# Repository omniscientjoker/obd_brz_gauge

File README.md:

# OBD BRZ Gauge

A round ESP-IDF car gauge for the Waveshare ESP32-S3-Touch-LCD-1.85. It connects
to an ELM327-compatible BLE OBD adapter, reads vehicle data, and renders a
touch UI with LVGL.

基于 ESP-IDF 的圆形车载仪表，硬件为微雪 Waveshare ESP32-S3-Touch-LCD-1.85。
通过 BLE 连接兼容 ELM327 的 OBD 适配器读取车辆数据，用 LVGL 渲染触控界面。

**[效果演示 / Demo video](https://www.douyin.com/video/7614174567678984187)**

> Based on [zhaizhaitao/open_obd_dsp](https://github.com/zhaizhaitao/open_obd_dsp)
> by zhaizhaitao ([Bilibili demo](https://www.bilibili.com/video/BV18oHXz6EiQ/)).
> This is a derivative with additional vehicle profiles, multi-gauge support and
> a theming system.
>
> 本项目基于 [zhaizhaitao/open_obd_dsp](https://github.com/zhaizhaitao/open_obd_dsp)
> 二次开发，原作者 zhaizhaitao（[B 站演示](https://www.bilibili.com/video/BV18oHXz6EiQ/)）。
> 本仓库新增了多车型适配、三连表联动和主题系统。

---

## ⚠️ Branch Notice / 分支说明

This repository has two main branches with **incompatible partition layouts**:

- **`main`** — Stable branch, themes compiled into firmware
- **`theme-upgrade`** — Experimental branch with runtime-loadable themes (4MB theme partition)

⚠️ You **cannot** OTA upgrade between branches. See [docs/BRANCH_COMPARISON.md](docs/BRANCH_COMPARISON.md) for details.

本仓库有两个主要分支，**分区布局不兼容**：

- **`main`** — 稳定分支，主题编译进固件
- **`theme-upgrade`** — 实验分支，支持运行时加载主题（4MB 主题分区）

⚠️ 两个分支之间**无法通过 OTA 互相升级**。详见 [docs/BRANCH_COMPARISON.md](docs/BRANCH_COMPARISON.md)。

---

## 📖 Documentation / 文档索引

**Start here / 从这里开始**

| Document | What it covers / 内容 |
|----------|----------------------|
| [docs/README.zh-CN.md](docs/README.zh-CN.md) | **完整中文说明** — 功能、依赖、编译烧录、适配要点 |
| [docs/README.en.md](docs/README.en.md) | **Full English guide** — features, requirements, build and flash |
| [docs/BRANCH_COMPARISON.md](docs/BRANCH_COMPARISON.md) | **Branch differences** — main vs theme-upgrade partition layouts / 分支差异对比 |
| [docs/APP_INTEGRATION.md](docs/APP_INTEGRATION.md) | App/device manifest, firmware validation, single-slot boot animation / App 对接、硬件校验、单槽开机动画 |
| [firmware/README.md](firmware/README.md) | Pre-built binaries and flash addresses / 预编译固件与烧录地址 |
| [CHANGELOG.md](CHANGELOG.md) | Changelog / 更新日志（中英双语） |

**Vehicles & OBD / 车辆适配与 OBD**

| Document | What it covers / 内容 |
|----------|----------------------|
| [docs/VEHICLE_CONFIG.md](docs/VEHICLE_CONFIG.md) | **Adding a vehicle profile** / 新增车型看这篇（中英对照） |
| [docs/OBD_TROUBLESHOOTING.md](docs/OBD_TROUBLESHOOTING.md) | No data / won't connect — diagnosis / 连不上或没数据时的排查 |
| [docs/AUTO_PROTOCOL_DETECTION.md](docs/AUTO_PROTOCOL_DETECTION.md) | Protocol auto-detection: usage, FAQ, debugging / 自动协议检测：用法、常见问题、调试 |
| [docs/BRZ_ZD8_PROTOCOL_GUIDE.md](docs/BRZ_ZD8_PROTOCOL_GUIDE.md) | BRZ ZD8 (Gen2) protocol diagnosis / ZD8 协议诊断 |
| [docs/OBD_PROTOCOL_COMPOSITION_DESIGN.zh-CN.md](docs/OBD_PROTOCOL_COMPOSITION_DESIGN.zh-CN.md) | **Multi-protocol composition architecture** / 多协议组合、覆盖和迁移架构 |
| [docs/FORD_TPMS_CAPTURE.md](docs/FORD_TPMS_CAPTURE.md) | Ford TPMS UDS/CAN validation procedure / 福特胎压 UDS/CAN 验证流程 |

**UI themes / 界面主题**

| Document | What it covers / 内容 |
|----------|----------------------|
| [themes/README.md](themes/README.md) | **Build a theme** — no C code needed / 做一套主题（中英双语） |
| [docs/THEMING.md](docs/THEMING.md) | Theme framework internals / 主题框架内部实现 |

Repository layout is in [this README](#repository-layout--目录结构) below.
目录结构见本文下方的[目录结构](#repository-layout--目录结构)一节。

---

## Status / 当前状态

| | |
|---|---|
| Hardware / 硬件 | Waveshare ESP32-S3-Touch-LCD-1.85 (360×360 round, 16 MB flash, 8 MB PSRAM) |
| Stack / 软件栈 | ESP-IDF 5.5.3, LVGL 8 |
| Link / 通信链路 | BLE + ELM327 — standard OBD PID; only ZN/C6 CAN keeps ATMA monitoring |
| Multi-gauge / 三连表 | One master + multiple slaves over ESP-NOW / 一主多从，ESP-NOW 联动 |
| OBD architecture / 架构 | Composed common rules + vehicle packs + special handlers, with legacy fallback / 通用规则、车型包、特殊处理器组合，保留兼容回退 |
| Verified on / 已验证 | Subaru BRZ ZN/C6 (fully); Ford Mondeo 2014 2.0T BCMii TPMS / BRZ ZN/C6 已完整验证；蒙迪欧 2014 2.0T BCMii 胎压已验证 |

**Vehicle profiles / 内置车型** (18) — full list in
[vehicle_profiles.c](main/app_obd_dsp/vehicle_profiles.c), selectable in Settings:

`OBD2 Generic` · `ZN/C6 CAN` · `ZN/C6 PID` · `ZD8 OBD` · `ZD8` · `MX-5 ND` ·
`BMW F/G` · `Supra A90` · `BMW G OBD` · `BMW E` · `JCW F56` · `MINI R55` ·
`POS 997.2` · `POS 997.1` · `GIULIA 2.0T` · `jeep` · `Honda Integra` ·
`Ford Mondeo 2014` (BCMii TPMS, validated)

## Highlights / 主要特性

- **CAN broadcast monitoring** — only `ZN/C6 CAN` bypasses PID polling for
  high-rate channels; the rest stay on OBD-only polling. / **CAN 广播帧监听** —— 仅 `ZN/C6 CAN` 使用高速监听，其余车型保持 OBD 轮询。
- **Single-thread ELM327 loop** — no mixed OBD/CAN parallel path; only `ZN/C6 CAN`
  uses ATMA, so the adapter does not get contended by dual polling. /
  **ELM327 单线程轮询** —— 不再混跑 OBD/CAN；只有 `ZN/C6 CAN` 走 ATMA，避免适配器抢占和数据延迟。
- **Brake-temp / oil-pressure alarm throttle** — these two alarms are rate-limited
  to once every 30 seconds. / **刹车温度 / 油压报警节流** —— 两项报警限制为 30 秒一次，减少刷屏。
- **Multi-gauge over ESP-NOW** — one board reads OBD and broadcasts; the others
  display with zero extra OBD load, paired over real BLE. /
  **三连表** —— 主表读 OBD 广播，从表零额外负载显示，走真蓝牙配对。
- **Data-driven themes** — a theme is a folder with a manifest plus optional
  artwork; no C code. / **配置驱动主题** —— 一个文件夹 + 一份清单，不用写 C。
- **BLE device manifest** — a read-only GATT service exposes hardware/build info so the App can reject mismatched firmware before flashing. / **BLE 设备清单** —— 只读 GATT 服务暴露硬件/构建信息，App 刷写前先做硬件匹配校验。
- **RPM warning, incl. linked mode** — three gauges light up in sequence as revs
  climb. / **转速报警（含联动模式）** —— 三块表随转速依次亮起。
- Manufacturer oil-temp paths beyond PID 01 5C (Mode 21/22, Mazda, MINI/BMW),
  per-vehicle protocol lock, gear from CAN when available.
- **Composable OBD rules** — common SAE PID rules, vehicle-specific UDS/CAN packs,
  stable-ID overrides, special-handler capabilities, and fail-closed plan validation.
- Self-healing BLE: re-initializes on reconnect and recovers when data stalls —
  no manual reconnect after ignition. / 数据中断自愈，上车通电无需手动重连。

Full feature lists: [中文](docs/README.zh-CN.md#功能概览) ·
[English](docs/README.en.md#features)

## Quick Start / 快速开始

### Build from source / 从源码编译

```bash
git clone https://github.com/steveEcode/obd_brz_gauge.git
cd obd_brz_gauge
./tools/build_gauge_firmware.sh master
./tools/build_gauge_firmware.sh slave
python3 tools/gen_release.py
```

### Flash pre-built firmware / 烧录预编译固件

Activate ESP-IDF v5.5.3 before building. Master and slave use separate build
directories and configurations. See [firmware/README.md](firmware/README.md).

激活 ESP-IDF v5.5.3 后编译。主表和从表分别构建；`tools/release.sh` 可一次构建并打包两套固件。

Flash the master package / 烧录主表包：

```bash
cd firmware/release/master
python -m esptool --chip esp32s3 -p PORT -b 460800 \
  --before default_reset --after hard_reset write_flash @flash_args
```

For a slave, run the same command inside `firmware/release/slave`.
从表在 `firmware/release/slave` 目录中执行同样命令。两块从表刷入同一份固件。

**Notes / 说明:**
- Replace `PORT` with your serial port (e.g., `COM3` on Windows, `/dev/ttyUSB0` on Linux, `/dev/cu.usbserial-*` on macOS)
- Requires [esptool.py](https://github.com/espressif/esptool) installed: `pip install esptool`
- Writes the specified partitions; preserves NVS and theme data
- For subsequent OTA updates, use the companion mobile app

- 将 `PORT` 替换为你的串口（Windows: `COM3`，Linux: `/dev/ttyUSB0`，macOS: `/dev/cu.usbserial-*`）
- 需要安装 [esptool.py](https://github.com/espressif/esptool)：`pip install esptool`
- 烧录指定分区，保留 NVS 设置和主题数据
- 后续升级请使用配套手机 App 进行 OTA 更新

## Repository Layout / 目录结构

| Path | Contents |
|------|----------|
| [main/app_main.c](main/app_main.c) | Entry point: hardware, LVGL, BLE and task startup |
| [main/app_obd_dsp](main/app_obd_dsp) | OBD data cache, vehicle profiles, CAN decoders, boot media |
| [main/bsp_obd_dsp](main/bsp_obd_dsp) | Board support: BLE, NVS, LCD, touch, I2C, IO expander, ESP-NOW |
| [main/export_path](main/export_path) | LVGL UI (SquareLine export) + theme framework |
| [themes](themes) | Theme manifests and artwork / 主题清单与素材 |
| [bootmedia](bootmedia) | Boot animation blocks (SPIFFS partition source) |
| [tools](tools) | Helper scripts: theme codegen, image conversion, boot blocks |
| [firmware/release](firmware/release) | Pre-compiled binaries |
| [model](model) | 3D printable housings, gauge pods and brackets |
| [docs](docs) | Documentation (see index above) |

## 3D Models / 开源模型

| File | Description |
|------|-------------|
| `model/esp32_1.85_weixue/housing.stl` | Board housing / 开发板外壳 |
| `model/Subaru/brz_zc_n6/triple_gauge_pod.stp` | BRZ ZN/C6 triple gauge pod / 三连表底座 |
| `model/Subaru/brz_zc_n6/passenger_dashboard_scan.stl` | BRZ ZN/C6 passenger dash scan (fitting reference) / 副驾仪表台扫描件 |
| `model/mazda/mx5_nd/air_vent_bracket.stl` | MX-5 ND air vent bracket / 出风口支架 |

## Porting Notes / 适配提醒

This repository contains board-specific adaptation and UI resources. Porting to
another ESP32-S3 board means revisiting pin mapping and display settings
([main/bsp_obd_dsp](main/bsp_obd_dsp)); porting to another car means
re-verifying BLE services, PIDs and response parsing
([docs/VEHICLE_CONFIG.md](docs/VEHICLE_CONFIG.md)).

仓库内是针对当前开发板的适配代码和 UI 资源。换开发板需要重新检查引脚定义和屏幕参数；
换车型或适配器需要重新验证 BLE 服务、PID 和返回数据解析。

## Acknowledgments / 致谢

- [Hokori23](https://github.com/Hokori23) — performance optimization suggestions
  and contributions (NVS flush lock hold-time, page-aware refresh cadence, OBD
  polling throughput). / 性能优化建议与贡献。
- [timurrrr/ft86](https://github.com/timurrrr/ft86) — comprehensive FT86 CAN bus
  documentation (Gen1/Gen2 CAN ID mappings and byte-level decoding formulas),
  which made the CAN broadcast monitoring possible. /
  提供了完整的 FT86 CAN 总线文档，使 CAN 广播帧监听得以实现。

## License / 开源协议

This project is licensed under the **GNU General Public License v3.0 (GPLv3)**.

本项目采用 **GNU 通用公共许可证 v3.0 (GPLv3)** 开源协议。

- You are free to use, modify, and distribute this software.
- If you distribute modified versions, you must also release the source code under GPLv3.
- See [LICENSE](LICENSE) for the full license text.

**简单来说**：
- ✅ 可以自由使用、修改和分发本软件
- ⚠️ 如果分发修改版本，必须同样以GPLv3协议开源代码
- 🔒 增强了防专利条款和Tivoization保护
- 📄 完整协议文本见 [LICENSE](LICENSE) 文件

```
Copyright (C) 2024-2026  steveEcode and contributors

This program is free software: you can redistribute it and/or modify
it under the terms of the GNU General Public License as published by
the Free Software Foundation, either version 3 of the License, or
(at your option) any later version.

This program is distributed in the hope that it will be useful,
but WITHOUT ANY WARRANTY; without even the implied warranty of
MERCHANTABILITY or FITNESS FOR A PARTICULAR PURPOSE.  See the
GNU General Public License for more details.
```

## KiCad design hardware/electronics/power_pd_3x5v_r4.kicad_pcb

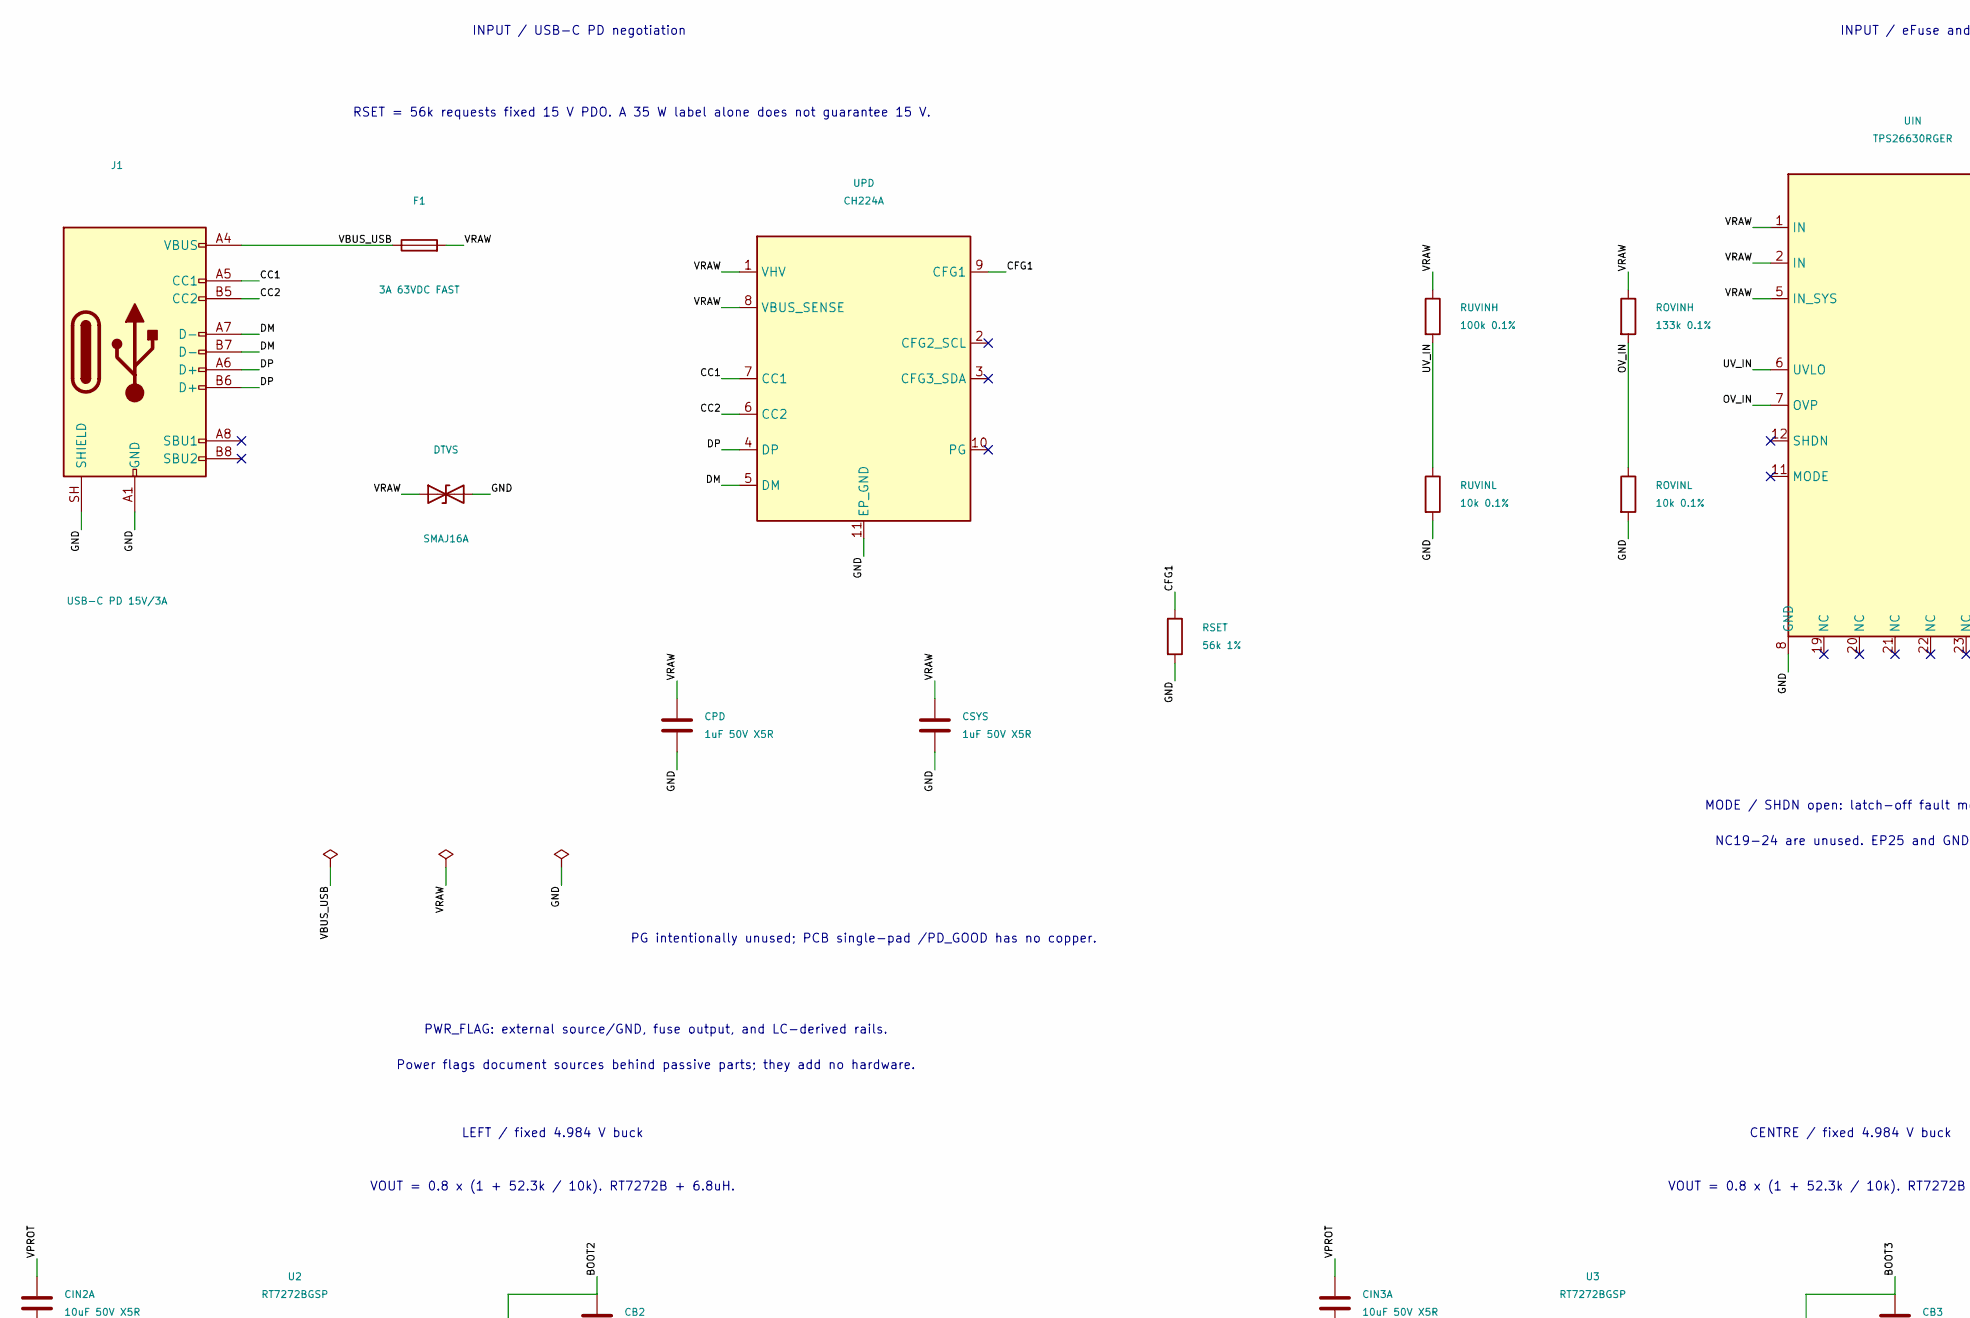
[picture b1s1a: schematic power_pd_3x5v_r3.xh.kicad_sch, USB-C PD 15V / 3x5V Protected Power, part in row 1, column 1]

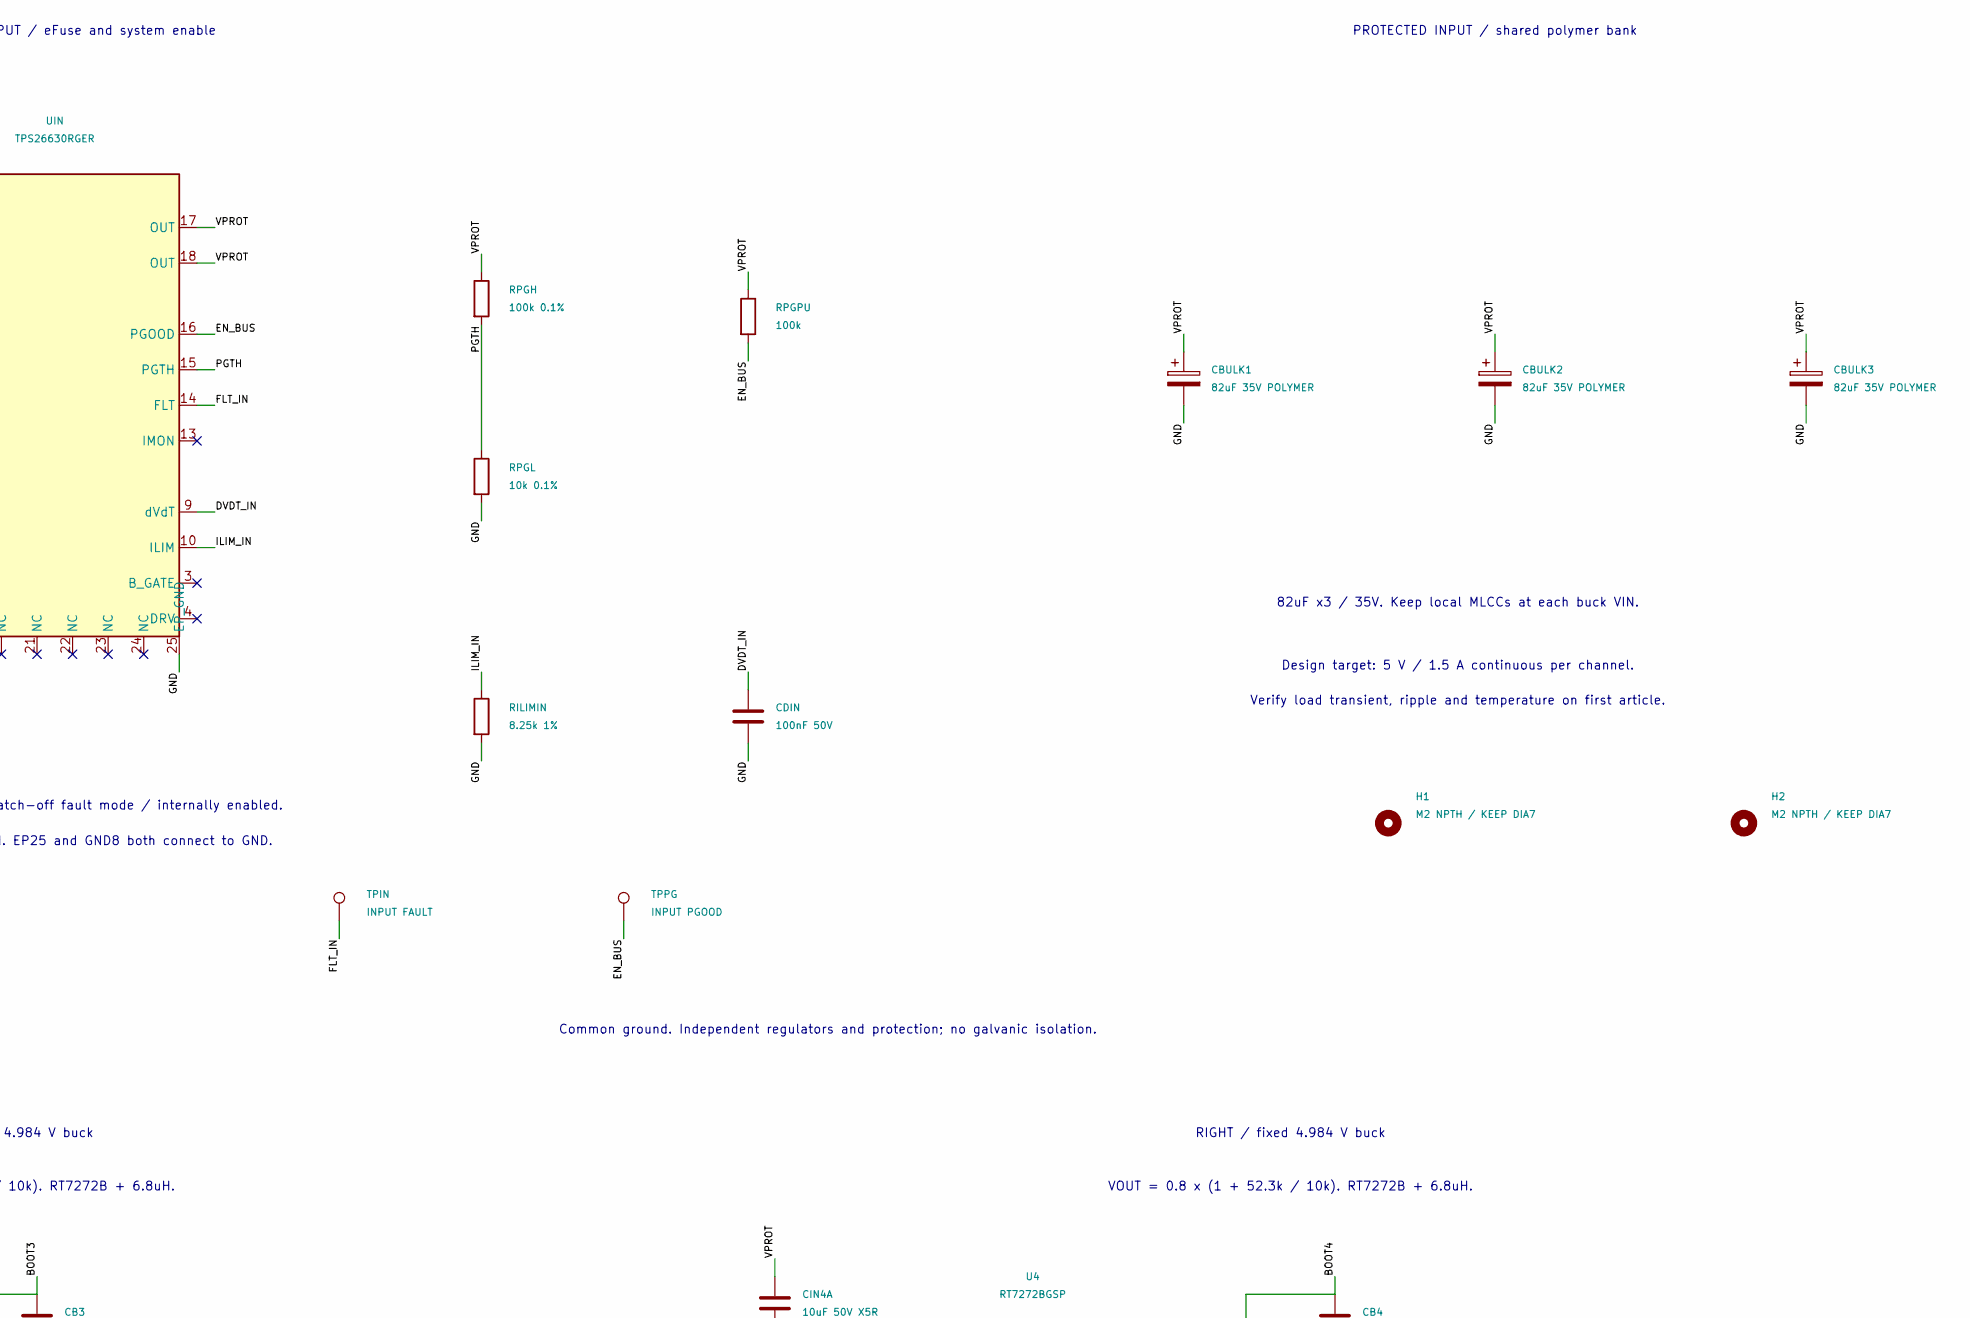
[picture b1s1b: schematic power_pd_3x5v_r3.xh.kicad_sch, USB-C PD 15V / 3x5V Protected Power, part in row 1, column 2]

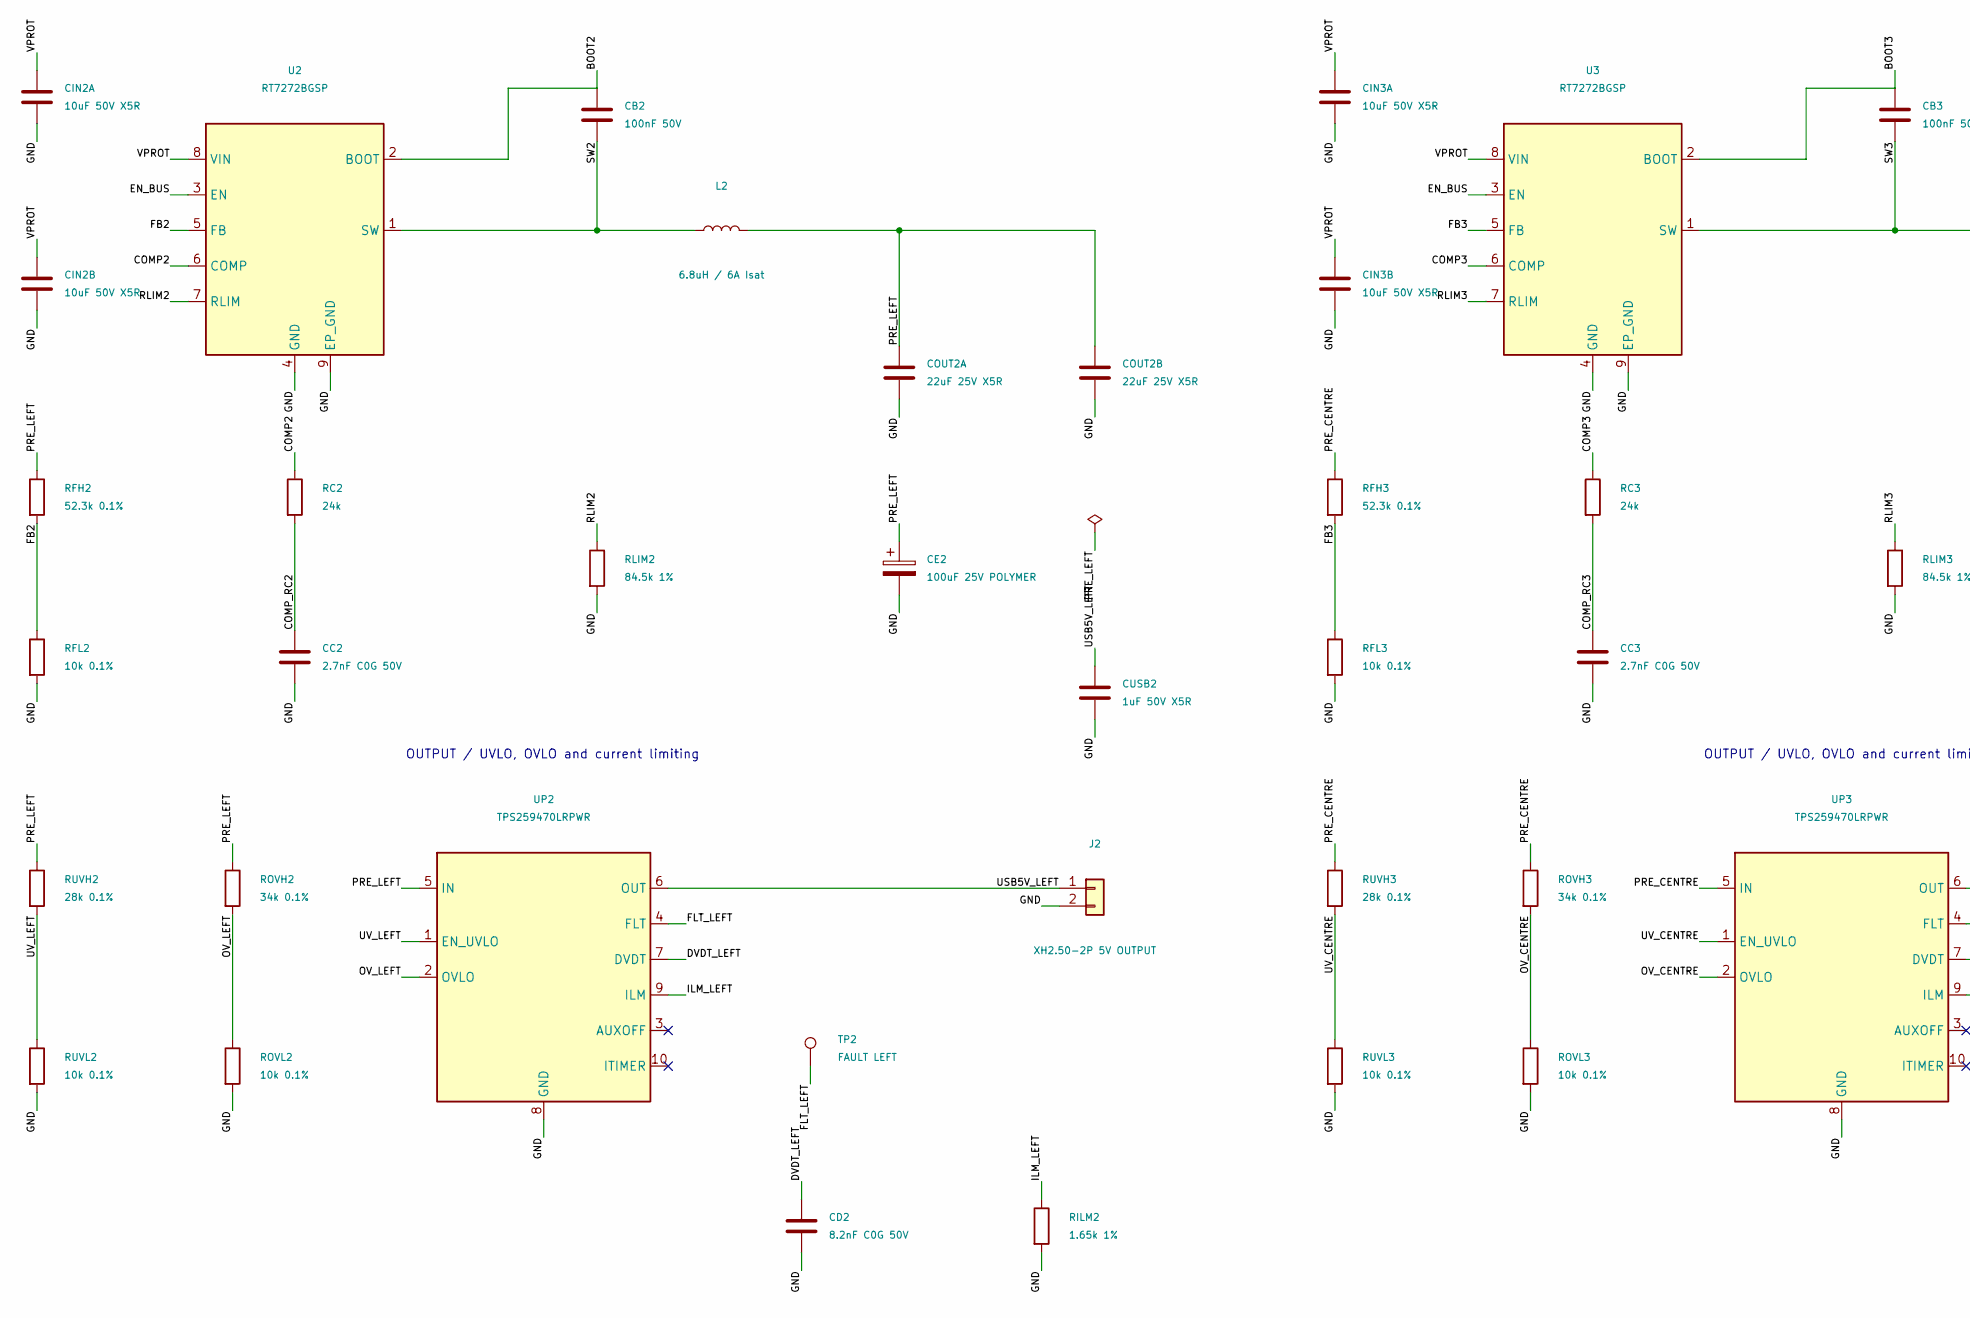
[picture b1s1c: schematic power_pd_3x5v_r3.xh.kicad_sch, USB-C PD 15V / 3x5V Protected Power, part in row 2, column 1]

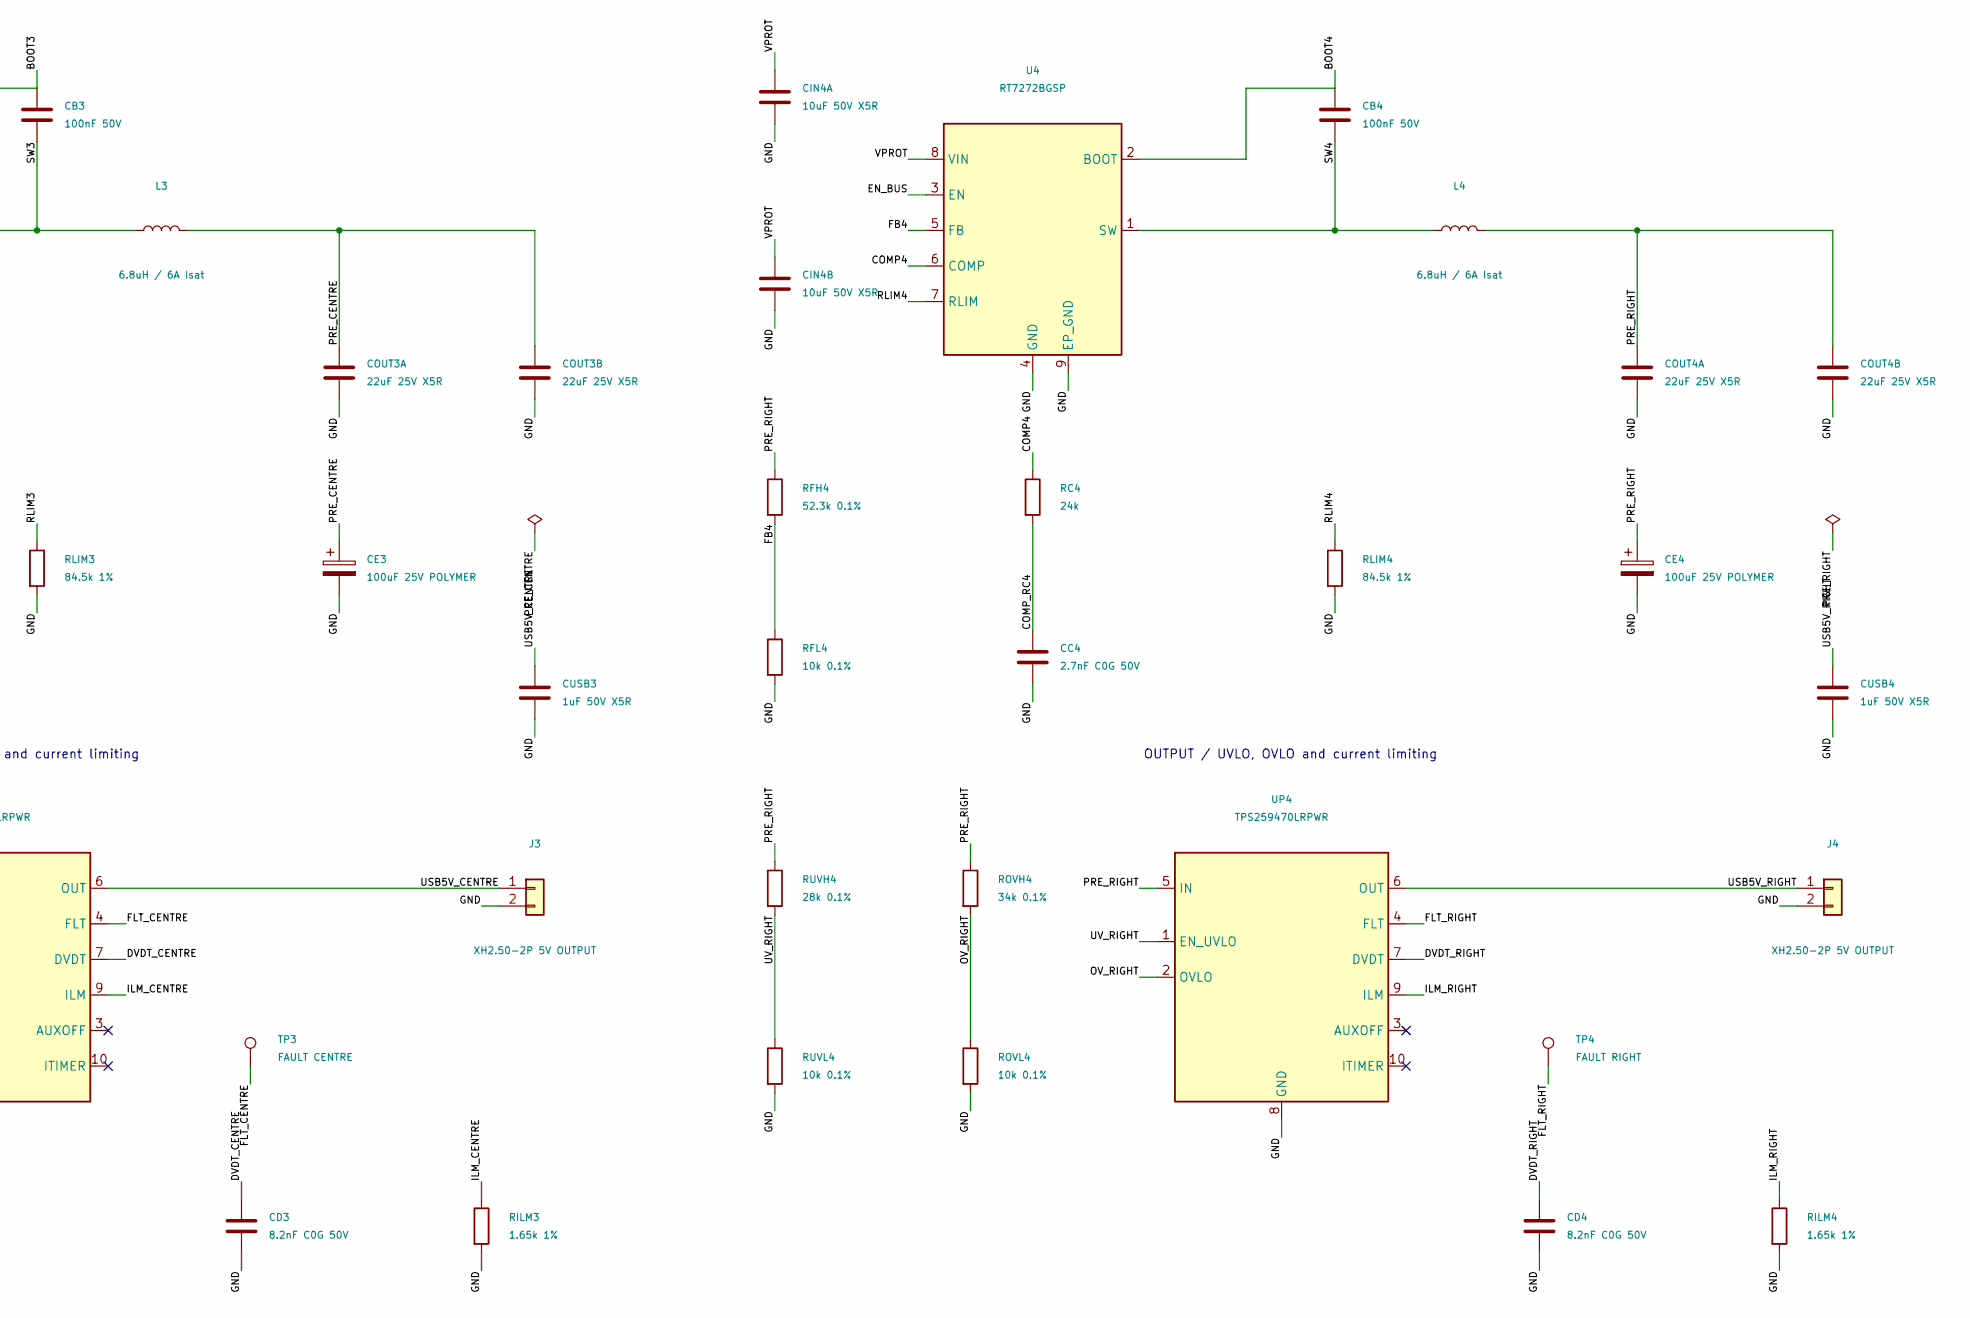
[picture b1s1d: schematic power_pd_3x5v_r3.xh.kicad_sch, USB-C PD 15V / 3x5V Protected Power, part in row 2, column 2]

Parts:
CB2, CB3, CB4: 100nF 50V; C_0603_1608Metric; MPN GRM188R71H104KA93D
CBULK1, CBULK2, CBULK3: 82uF 35V POLYMER; CP_Elec_8x6.9; MPN 35SVPK82M
CC2, CC3, CC4: 2.7nF C0G 50V; C_0603_1608Metric; MPN GRM1885C1H272JA01D
CD2, CD3, CD4: 8.2nF C0G 50V; C_0603_1608Metric; MPN GRM1885C1H822JA01D
CDIN: 100nF 50V; C_0603_1608Metric; MPN GRM188R71H104KA93D
CE2, CE3, CE4: 100uF 25V POLYMER; CP_Elec_8x6.9; MPN 25SVPF100M
CIN2A, CIN2B, CIN3A, CIN3B, CIN4A, CIN4B: 10uF 50V X5R; C_1206_3216Metric; MPN GRM31CR61H106KA12L
COUT2A, COUT2B, COUT3A, COUT3B, COUT4A, COUT4B: 22uF 25V X5R; C_1206_3216Metric; MPN GRM31CR61E226KE15L
CPD: 1uF 50V X5R; C_0603_1608Metric; MPN GRM188R61H105KAALD
CSYS: 1uF 50V X5R; C_0603_1608Metric; MPN GRM188R61H105KAALD
CUSB2, CUSB3, CUSB4: 1uF 50V X5R; C_0603_1608Metric; MPN GRM188R61H105KAALD
DTVS: SMAJ16A; D_SMA; MPN SMAJ16A-E3/61
F1: 3A 63VDC FAST; SF_1206F_Recommended; MPN SF-1206F300-2
H1, H2: M2 NPTH / KEEP DIA7; M2_NPTH_2.4mm
J1: USB-C PD 15V/3A; USB_C_Receptacle_GCT_USB4085; MPN USB4085-GF-A
J2, J3, J4: XH2.50-2P 5V OUTPUT; JST_XH_S2B-XH-A_1x02_P2.50mm_Horizontal_Assembly; MPN S2B-XH-A(LF)(SN)
L2, L3, L4: 6.8uH / 6A Isat; L_Coilcraft_XAL5050-XXX; MPN XAL5050-682MEC
RC2, RC3, RC4: 24k; R_0603_1608Metric; MPN TNPW060324K0FEEA
RFH2, RFH3, RFH4: 52.3k 0.1%; R_0603_1608Metric; MPN TNPW060352K3BEEA
RFL2, RFL3, RFL4: 10k 0.1%; R_0603_1608Metric; MPN TNPW060310K0BEEA
RILIMIN: 8.25k 1%; R_0603_1608Metric; MPN TNPW06038K25FEEA
RILM2, RILM3, RILM4: 1.65k 1%; R_0603_1608Metric; MPN TNPW06031K65FEEA
RLIM2, RLIM3, RLIM4: 84.5k 1%; R_0603_1608Metric; MPN TNPW060384K5FEEA
ROVH2, ROVH3, ROVH4: 34k 0.1%; R_0603_1608Metric; MPN TNPW060334K0BEEA
ROVINH: 133k 0.1%; R_0402_1005Metric; MPN CRT0402-BY-1333GLF
ROVINL: 10k 0.1%; R_0402_1005Metric; MPN TNPW040210K0BEED
ROVL2, ROVL3, ROVL4: 10k 0.1%; R_0603_1608Metric; MPN TNPW060310K0BEEA
RPGH: 100k 0.1%; R_0603_1608Metric; MPN TNPW0603100KBEEA
RPGL: 10k 0.1%; R_0603_1608Metric; MPN TNPW060310K0BEEA
RPGPU: 100k; R_0603_1608Metric; MPN TNPW0603100KFEEA
RSET: 56k 1%; R_0603_1608Metric; MPN TNPW060356K0FEEA
RUVH2, RUVH3, RUVH4: 28k 0.1%; R_0603_1608Metric; MPN TNPW060328K0BEEA
RUVINH: 100k 0.1%; R_0402_1005Metric; MPN TNPW0402100KBEED
RUVINL: 10k 0.1%; R_0402_1005Metric; MPN TNPW040210K0BEED
RUVL2, RUVL3, RUVL4: 10k 0.1%; R_0603_1608Metric; MPN TNPW060310K0BEEA
TP2: FAULT LEFT; TestPoint_Pad_D1.0mm
TP3: FAULT CENTRE; TestPoint_Pad_D1.0mm
TP4: FAULT RIGHT; TestPoint_Pad_D1.0mm
TPIN: INPUT FAULT; TestPoint_Pad_D1.0mm
TPPG: INPUT PGOOD; TestPoint_Pad_D1.0mm
U2, U3, U4: RT7272BGSP; RT7272BGSP_PSOP8_Option2; MPN RT7272BGSP
UIN: TPS26630RGER; Texas_RGE0024H_VQFN-24-1EP_4x4mm_P0.5mm_EP2.7x2.7mm_Assembly; MPN TPS26630RGER
UP2, UP3, UP4: TPS259470LRPWR; TI_RPW0010A; MPN TPS259470LRPWR
UPD: CH224A; SSOP-10-1EP_3.9x4.9mm_P1mm_EP2.1x3.3mm; MPN CH224A

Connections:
/BOOT2: CB2.1, U2.2 (BOOT)
/BOOT3: CB3.1, U3.2 (BOOT)
/BOOT4: CB4.1, U4.2 (BOOT)
/CC1: J1.A5 (CC1), UPD.7 (CC1)
/CC2: J1.B5 (CC2), UPD.6 (CC2)
/CFG1: RSET.1, UPD.9 (CFG1)
/COMP2: RC2.1, U2.6 (COMP)
/COMP3: RC3.1, U3.6 (COMP)
/COMP4: RC4.1, U4.6 (COMP)
/COMP_RC2: CC2.1, RC2.2
/COMP_RC3: CC3.1, RC3.2
/COMP_RC4: CC4.1, RC4.2
/DM: J1.A7 (D-), J1.B7 (D-), UPD.5 (DM)
/DP: J1.A6 (D+), J1.B6 (D+), UPD.4 (DP)
/DVDT_CENTRE: CD3.1, UP3.7 (DVDT)
/DVDT_IN: CDIN.1, UIN.9 (dVdT)
/DVDT_LEFT: CD2.1, UP2.7 (DVDT)
/DVDT_RIGHT: CD4.1, UP4.7 (DVDT)
/EN_BUS: RPGPU.2, TPPG.1, U2.3 (EN), U3.3 (EN), U4.3 (EN), UIN.16 (PGOOD)
/FB2: RFH2.2, RFL2.1, U2.5 (FB)
/FB3: RFH3.2, RFL3.1, U3.5 (FB)
/FB4: RFH4.2, RFL4.1, U4.5 (FB)
/FLT_CENTRE: TP3.1, UP3.4 (FLT)
/FLT_IN: TPIN.1, UIN.14 (FLT)
/FLT_LEFT: TP2.1, UP2.4 (FLT)
/FLT_RIGHT: TP4.1, UP4.4 (FLT)
/GND: CBULK1.2, CBULK2.2, CBULK3.2, CC2.2, CC3.2, CC4.2, CD2.2, CD3.2, CD4.2, CDIN.2, CE2.2, CE3.2, CE4.2, CIN2A.2, CIN2B.2, CIN3A.2, CIN3B.2, CIN4A.2, CIN4B.2, COUT2A.2, COUT2B.2, COUT3A.2, COUT3B.2, COUT4A.2, COUT4B.2, CPD.2, CSYS.2, CUSB2.2, CUSB3.2, CUSB4.2, DTVS.2 (A2), J1.A1 (GND), J1.A12 (GND), J1.B1 (GND), J1.B12 (GND), J1.SH (SHIELD), J2.2, J3.2, J4.2, RFL2.2, RFL3.2, RFL4.2, RILIMIN.2, RILM2.2, RILM3.2, RILM4.2, RLIM2.2, RLIM3.2, RLIM4.2, ROVINL.2, ROVL2.2, ROVL3.2, ROVL4.2, RPGL.2, RSET.2, RUVINL.2, RUVL2.2, RUVL3.2, RUVL4.2, U2.4 (GND), U2.9 (EP_GND), U3.4 (GND), U3.9 (EP_GND), U4.4 (GND), U4.9 (EP_GND), UIN.8 (GND), UIN.25 (EP_GND), UP2.8 (GND), UP3.8 (GND), UP4.8 (GND), UPD.11 (EP_GND)
/ILIM_IN: RILIMIN.1, UIN.10 (ILIM)
/ILM_CENTRE: RILM3.1, UP3.9 (ILM)
/ILM_LEFT: RILM2.1, UP2.9 (ILM)
/ILM_RIGHT: RILM4.1, UP4.9 (ILM)
/OV_CENTRE: ROVH3.2, ROVL3.1, UP3.2 (OVLO)
/OV_IN: ROVINH.2, ROVINL.1, UIN.7 (OVP)
/OV_LEFT: ROVH2.2, ROVL2.1, UP2.2 (OVLO)
/OV_RIGHT: ROVH4.2, ROVL4.1, UP4.2 (OVLO)
/PD_GOOD: UPD.10 (PG)
/PGTH: RPGH.2, RPGL.1, UIN.15 (PGTH)
/PRE_CENTRE: CE3.1, COUT3A.1, COUT3B.1, L3.2, RFH3.1, ROVH3.1, RUVH3.1, UP3.5 (IN)
/PRE_LEFT: CE2.1, COUT2A.1, COUT2B.1, L2.2, RFH2.1, ROVH2.1, RUVH2.1, UP2.5 (IN)
/PRE_RIGHT: CE4.1, COUT4A.1, COUT4B.1, L4.2, RFH4.1, ROVH4.1, RUVH4.1, UP4.5 (IN)
/RLIM2: RLIM2.1, U2.7 (RLIM)
/RLIM3: RLIM3.1, U3.7 (RLIM)
/RLIM4: RLIM4.1, U4.7 (RLIM)
/SW2: CB2.2, L2.1, U2.1 (SW)
/SW3: CB3.2, L3.1, U3.1 (SW)
/SW4: CB4.2, L4.1, U4.1 (SW)
/USB5V_CENTRE: CUSB3.1, J3.1, UP3.6 (OUT)
/USB5V_LEFT: CUSB2.1, J2.1, UP2.6 (OUT)
/USB5V_RIGHT: CUSB4.1, J4.1, UP4.6 (OUT)
/UV_CENTRE: RUVH3.2, RUVL3.1, UP3.1 (EN_UVLO)
/UV_IN: RUVINH.2, RUVINL.1, UIN.6 (UVLO)
/UV_LEFT: RUVH2.2, RUVL2.1, UP2.1 (EN_UVLO)
/UV_RIGHT: RUVH4.2, RUVL4.1, UP4.1 (EN_UVLO)
/VBUS_USB: F1.1, J1.A4 (VBUS), J1.A9 (VBUS), J1.B4 (VBUS), J1.B9 (VBUS)
/VPROT: CBULK1.1, CBULK2.1, CBULK3.1, CIN2A.1, CIN2B.1, CIN3A.1, CIN3B.1, CIN4A.1, CIN4B.1, RPGH.1, RPGPU.1, U2.8 (VIN), U3.8 (VIN), U4.8 (VIN), UIN.17 (OUT), UIN.18 (OUT)
/VRAW: CPD.1, CSYS.1, DTVS.1 (A1), F1.2, ROVINH.1, RUVINH.1, UIN.1 (IN), UIN.2 (IN), UIN.5 (IN_SYS), UPD.1 (VHV), UPD.8 (VBUS_SENSE)

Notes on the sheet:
PG intentionally unused; PCB single-pad /PD_GOOD has no copper.
INPUT / USB-C PD negotiation
INPUT / eFuse and system enable
PROTECTED INPUT / shared polymer bank
RSET = 56k requests fixed 15 V PDO. A 35 W label alone does not guarantee 15 V.
MODE / SHDN open: latch-off fault mode / internally enabled.
NC19-24 are unused. EP25 and GND8 both connect to GND.
82uF x3 / 35V. Keep local MLCCs at each buck VIN.
Design target: 5 V / 1.5 A continuous per channel.
Verify load transient, ripple and temperature on first article.
PWR_FLAG: external source/GND, fuse output, and LC-derived rails.
Power flags document sources behind passive parts; they add no hardware.
Common ground. Independent regulators and protection; no galvanic isolation.
LEFT / fixed 4.984 V buck
VOUT = 0.8 x (1 + 52.3k / 10k). RT7272B + 6.8uH.
OUTPUT / UVLO, OVLO and current limiting
CENTRE / fixed 4.984 V buck
RIGHT / fixed 4.984 V buck
